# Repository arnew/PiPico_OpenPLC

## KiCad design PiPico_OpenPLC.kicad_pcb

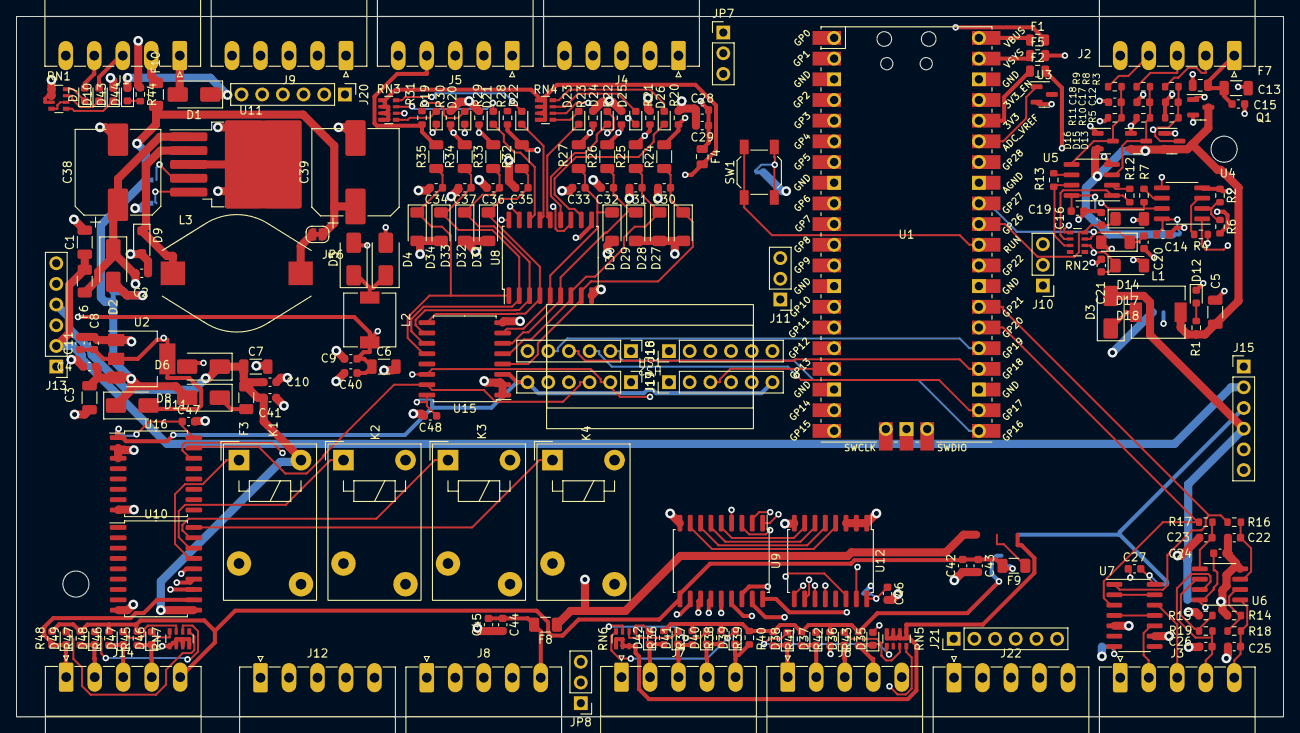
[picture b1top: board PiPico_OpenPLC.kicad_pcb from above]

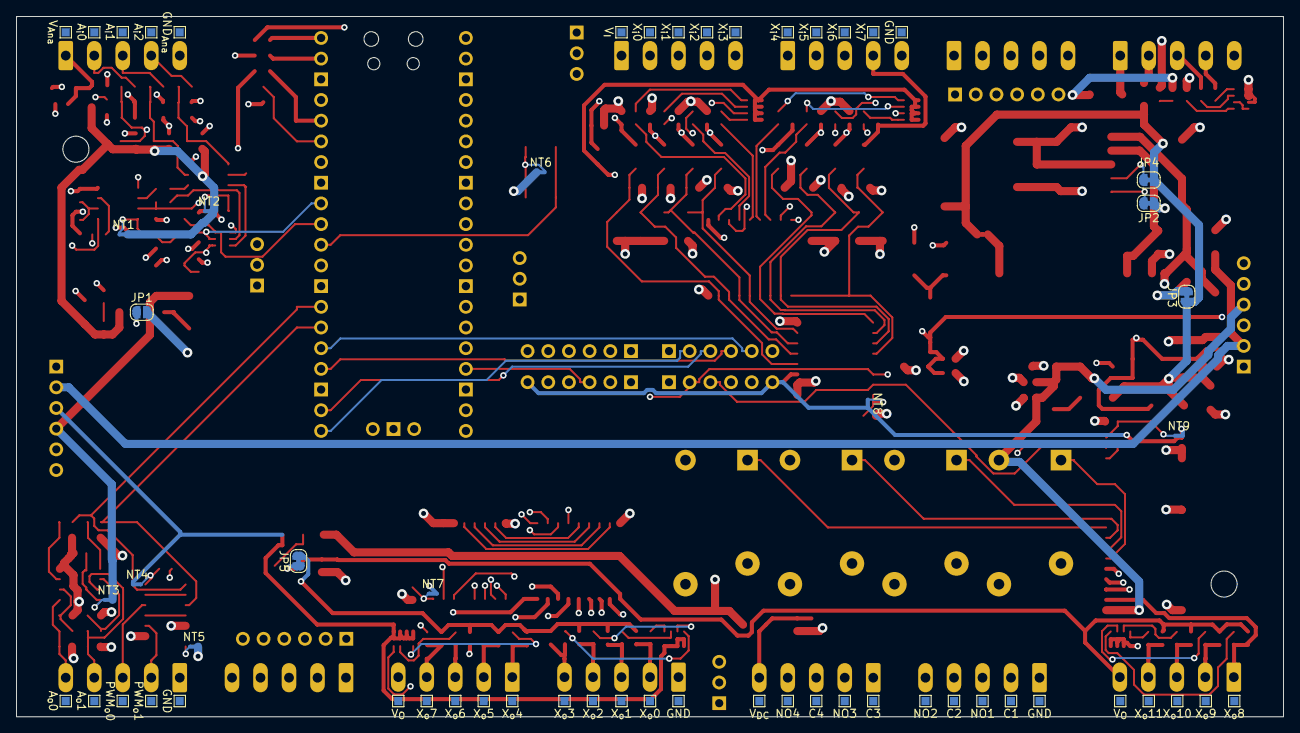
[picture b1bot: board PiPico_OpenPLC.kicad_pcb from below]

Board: 4 copper layers, 155.6 x 86.0 mm, 273 parts (59 on the bottom side), 193 nets.

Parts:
C1, C3, C5, C6, C7, C13: 50V 10uF X5R; C_1206_3216Metric
C2, C4, C9, C10, C11, C14, C15, C19, C24, C27, C29, C43, C44, C46, C47, C48: 50V 100nF X7R; C_0603_1608Metric
C8, C22, C23, C28, C42, C45: 10V 10uF X5R; C_0603_1608Metric
C12, C16, C17, C18, C20, C21, C25, C26, C30, C31, C32, C33, C34, C35, C36, C37, C40, C41: 50V 10nF X7R; C_0603_1608Metric
C38: 220uF 50V 105C; CP_Elec_10x10
C39: 680uF 25V 105C; CP_Elec_10x10.5
D1, D2, D3, D4, D5, D6, D8, D11: SS34; D_SMA
D7, D10, D12, D19, D20, D21, D22, D23, D24, D25, D26, D35, D36, D37, D38, D39, D40, D41, D42, D43, D44, D46, D47, D48, D49: Red; LED_0603_1608Metric
D9: MBR340F; D_SOD-123F
D13, D15, D16: BAV99; SOT-23
D14, D17, D18, D27, D28, D29, D30, D31, D32, D33, D34: ZMM3V3; D_MiniMELF
F1, F2, F4, F5, F7: 33V 100mA; Fuse_0805_2012Metric
F3, F6, F8, F9, F10: 16V 2A; Fuse_1206_3216Metric
H1, H4: MountingHole; MountingHole_3.2mm_M3
HS1, HS2: Submodule
J1, J2, J3, J4, J5, J6, J7, J8, J9, J12, J14, J22: 5 Pin 3.5mm; PhoenixContact_MC_1,5_5-G-3.5_1x05_P3.50mm_Horizontal
J10, J11: Conn_01x03_Male; PinHeader_1x03_P2.54mm_Vertical
J13, J15, J16, J17, J18, J19, J20, J21: Conn_01x06_Male; PinHeader_1x06_P2.54mm_Vertical
JP1: GND <-> GND_{Ana}; SolderJumper-2_P1.3mm_Open_RoundedPad1.0x1.5mm
JP2, JP3, JP4, JP5, JP6: Jumper_2_Bridged; SolderJumper-2_P1.3mm_Bridged_RoundedPad1.0x1.5mm
JP7: 5V < V_{I} > V_{DC}; PinHeader_1x03_P2.54mm_Vertical
JP8: 5V < V_{IO} > V_{DC}; PinHeader_1x03_P2.54mm_Vertical
K1, K2, K3, K4: HF32F/xxx-Z; Relay_SPST_Hongfa_HF32F-Z
L1, L2: 6.8uH; L_6.3x6.3_H3
L3: 150uH 1.5A; L_Bourns_SDR1806
N1: Housing; APRA 449-370-55
NT1, NT2, NT3, NT4, NT5, NT6, NT7, NT8, NT9: NetTie_2; NetTie-2_SMD_Pad0.5mm
Q1: MMBT2222A 1P; SOT-23
R1: 1k; R_0603_1608Metric
R2, R5, R10, R11, R14, R15: 4.3k; R_0603_1608Metric
R3, R4, R6, R7, R8, R9, R12, R13, R16, R17, R18, R19, R20, R21, R22, R23, R28, R29, R30, R31, R44: 10k; R_0603_1608Metric
R24, R25, R26, R27, R32, R33, R34, R35: 4.7k; R_1206_3216Metric
R36, R37, R38, R39, R40, R41, R42, R43, R45, R46, R47, R48: 100k; R_0603_1608Metric
RN1: 1k; R_Array_Convex_4x0603
RN2: 4k7; R_Array_Convex_4x0603
RN3, RN4, RN5, RN6, RN7: 470; R_Array_Convex_4x0603
SW1: TS1187; SW_SPST_SKQG_WithStem
TP1: X_{o}1; TestPoint_Pad_1.0x1.0mm
TP2: X_{o}2; TestPoint_Pad_1.0x1.0mm
TP3: V_{DC}; TestPoint_Pad_1.0x1.0mm
TP4: X_{o}3; TestPoint_Pad_1.0x1.0mm
TP5: X_{o}4; TestPoint_Pad_1.0x1.0mm
TP6: X_{o}5; TestPoint_Pad_1.0x1.0mm
TP7: X_{o}6; TestPoint_Pad_1.0x1.0mm
TP8: X_{o}7; TestPoint_Pad_1.0x1.0mm
TP9: X_{o}8; TestPoint_Pad_1.0x1.0mm
TP10: X_{o}9; TestPoint_Pad_1.0x1.0mm
TP11: X_{o}10; TestPoint_Pad_1.0x1.0mm
TP12: X_{o}11; TestPoint_Pad_1.0x1.0mm
TP13: X_{o}0; TestPoint_Pad_1.0x1.0mm
TP14, TP17, TP27, TP28: GND; TestPoint_Pad_1.0x1.0mm
TP15, TP16: V_{O}; TestPoint_Pad_1.0x1.0mm
TP18: NO4; TestPoint_Pad_1.0x1.0mm
TP19: C4; TestPoint_Pad_1.0x1.0mm
TP20: NO3; TestPoint_Pad_1.0x1.0mm
TP21: C3; TestPoint_Pad_1.0x1.0mm
TP22: NO2; TestPoint_Pad_1.0x1.0mm
TP23: C2; TestPoint_Pad_1.0x1.0mm
TP24: NO1; TestPoint_Pad_1.0x1.0mm
TP25: C1; TestPoint_Pad_1.0x1.0mm
TP26: V_{I}; TestPoint_Pad_1.0x1.0mm
TP29: A_{o}0; TestPoint_Pad_1.0x1.0mm
TP30: A_{o}1; TestPoint_Pad_1.0x1.0mm
TP31: PWM_{o}0; TestPoint_Pad_1.0x1.0mm
TP32: X_{i}7; TestPoint_Pad_1.0x1.0mm
TP33: X_{i}6; TestPoint_Pad_1.0x1.0mm
TP34: X_{i}5; TestPoint_Pad_1.0x1.0mm
TP35: X_{i}4; TestPoint_Pad_1.0x1.0mm
TP36: X_{i}3; TestPoint_Pad_1.0x1.0mm
TP37: X_{i}2; TestPoint_Pad_1.0x1.0mm
TP38: X_{i}1; TestPoint_Pad_1.0x1.0mm
TP39: X_{i}0; TestPoint_Pad_1.0x1.0mm
TP40: PWM_{o}1; TestPoint_Pad_1.0x1.0mm
TP41: V_{Ana}; TestPoint_Pad_1.0x1.0mm
TP42: A_{i}0; TestPoint_Pad_1.0x1.0mm
TP43: A_{i}1; TestPoint_Pad_1.0x1.0mm
TP44: A_{i}2; TestPoint_Pad_1.0x1.0mm
TP45: GND_{Ana}; TestPoint_Pad_1.0x1.0mm
U1: Pico; RPi_Pico_SMD_TH
U2: AMS1117-5.0; SOT-223-3_TabPin2
U3: LM4040DBZ-3; SOT-23
U4, U5, U6: LM358; SOIC-8_3.9x4.9mm_P1.27mm
U7: 74HC14; SOIC-14_3.9x8.7mm_P1.27mm
U8, U9, U10: ULN2803A; SOIC-18W_7.5x11.6mm_P1.27mm
U11: LM2596S-12; TO-263-5_TabPin3
U12, U15, U16: PCF8574; SOIC-16W_7.5x10.3mm_P1.27mm

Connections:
+3V3: D7.2 (A), F2.2, J1.4, J10.1, J13.5, J15.5, J16.6, J17.6, J18.6, J19.6, NT7.2, NT8.2, NT9.2, U15.3 (A2), U16.1 (A0)
+5V: C8.1, C11.1, D4.2 (A), D10.2 (A), D11.2 (A), J1.3, U2.2 (VO)
+10V: C13.1, C15.1, F7.2, J2.1, TP41.1
+12V: C3.1, C4.1, C39.1, D8.2 (A), D11.1 (K), D43.2 (A), F10.2, JP3.1 (A), JP4.1 (A), JP6.1 (A), U2.3 (VI)
/1-Wire: J10.2, U1.29 (GPIO22)
/ADC0: C16.1, D14.1 (K), RN2.8 (R1.2), U1.31 (GPIO26_ADC0)
/ADC1: C20.1, D17.1 (K), RN2.7 (R2.2), U1.32 (GPIO27_ADC1)
/ADC2: C21.1, D18.1 (K), RN2.6 (R3.2), U1.34 (GPIO28_ADC2)
/Analog_Input/Ai0: J2.2, R3.1, TP42.1
/Analog_Input/Ai1: J2.3, R8.1, TP43.1
/Analog_Input/Ai2: J2.4, R9.1, TP44.1
/Analog_Output/Ao0: C25.1, J3.5, R18.2, TP29.1, U6.1
/Analog_Output/Ao1: C26.1, J3.4, R19.2, TP30.1, U6.7
/Di0: C30.1, D27.1 (K), R24.1, U8.8 (I8), U15.4 (P0)
/Di1: C31.1, D28.1 (K), R25.1, U8.7 (I7), U15.5 (P1)
/Di2: C32.1, D29.1 (K), R26.1, U8.6 (I6), U15.6 (P2)
/Di3: C33.1, D30.1 (K), R27.1, U8.5 (I5), U15.7 (P3)
/Di4: C35.1, D31.1 (K), R32.1, U8.4 (I4), U15.9 (P4)
/Di5: C36.1, D32.1 (K), R33.1, U8.3 (I3), U15.10 (P5)
/Di6: C37.1, D33.1 (K), R34.1, U8.2 (I2), U15.11 (P6)
/Di7: C34.1, D34.1 (K), R35.1, U8.1 (I1), U15.12 (P7)
/Digital_Input/Xi0: J4.2, R20.1, R24.2, TP39.1
/Digital_Input/Xi1: J4.3, R21.1, R25.2, TP38.1
/Digital_Input/Xi2: J4.4, R22.1, R26.2, TP37.1
/Digital_Input/Xi3: J4.5, R23.1, R27.2, TP36.1
/Digital_Input/Xi4: J5.1, R28.1, R32.2, TP35.1
/Digital_Input/Xi5: J5.2, R29.1, R33.2, TP34.1
/Digital_Input/Xi6: J5.3, R30.1, R34.2, TP33.1
/Digital_Input/Xi7: J5.4, R31.1, R35.2, TP32.1
/Digital_Output/Xo0: D42.1 (K), J7.2, R36.1, TP13.1, U9.11 (O8)
/Digital_Output/Xo1: D41.1 (K), J7.3, R37.1, TP1.1, U9.12 (O7)
/Digital_Output/Xo2: D40.1 (K), J7.4, R38.1, TP2.1, U9.13 (O6)
/Digital_Output/Xo3: D39.1 (K), J7.5, R39.1, TP4.1, U9.14 (O5)
/Digital_Output/Xo4: D38.1 (K), J6.1, R40.1, TP5.1, U9.15 (O4)
/Digital_Output/Xo5: D37.1 (K), J6.2, R41.1, TP6.1, U9.16 (O3)
/Digital_Output/Xo6: D36.1 (K), J6.3, R42.1, TP7.1, U9.17 (O2)
/Digital_Output/Xo7: D35.1 (K), J6.4, R43.1, TP8.1, U9.18 (O1)
/Digital_Output/Xo8: D49.1 (K), J14.1, R48.1, TP9.1, U10.11 (O8)
/Digital_Output/Xo9: D48.1 (K), J14.2, R47.1, TP10.1, U10.12 (O7)
/Digital_Output/Xo10: D47.1 (K), J14.3, R46.1, TP11.1, U10.13 (O6)
/Digital_Output/Xo11: D46.1 (K), J14.4, R45.1, TP12.1, U10.14 (O5)
/Digital_Output/Zo_0: J12.3, K1.NO, TP24.1
/Digital_Output/Zo_1: J12.5, K2.NO, TP22.1
/Digital_Output/Zo_2: J8.2, K3.NO, TP20.1
/Digital_Output/Zo_3: J8.4, K4.NO, TP18.1
/Digital_Output/Zp_0: J12.2, K1.C, TP25.1
/Digital_Output/Zp_1: J12.4, K2.C, TP23.1
/Digital_Output/Zp_2: J8.1, K3.C, TP21.1
/Digital_Output/Zp_3: J8.3, K4.C, TP19.1
/Digital_Output/z0: K1.A1, U10.15 (O4)
/Digital_Output/z1: K2.A1, U10.16 (O3)
/Digital_Output/z2: K3.A1, U10.17 (O2)
/Digital_Output/z3: K4.A1, U10.18 (O1)
/Do0: U9.8 (I8), U12.4 (P0)
/Do1: U9.7 (I7), U12.5 (P1)
/Do2: U9.6 (I6), U12.6 (P2)
/Do3: U9.5 (I5), U12.7 (P3)
/Do4: U9.4 (I4), U12.9 (P4)
/Do5: U9.3 (I3), U12.10 (P5)
/Do6: U9.2 (I2), U12.11 (P6)
/Do7: U9.1 (I1), U12.12 (P7)
/Do8: U10.8 (I8), U16.4 (P0)
/Do9: U10.7 (I7), U16.5 (P1)
/Do10: U10.6 (I6), U16.6 (P2)
/Do11: U10.5 (I5), U16.7 (P3)
/Do12: U10.4 (I4), U16.9 (P4)
/Do13: U10.3 (I3), U16.10 (P5)
/Do14: U10.2 (I2), U16.11 (P6)
/Do15: U10.1 (I1), U16.12 (P7)
/I2C0_SCL: J17.2, U1.7 (GPIO5), U12.14 (SCL), U15.14 (SCL), U16.14 (SCL)
/I2C0_SDA: J17.3, U1.6 (GPIO4), U12.15 (SDA), U15.15 (SDA), U16.15 (SDA)
/I2C1_SCL: J18.2, U1.5 (GPIO3)
/I2C1_SDA: J18.3, U1.4 (GPIO2)
/PWMo0: R17.1, U1.26 (GPIO20), U7.3
/PWMo1: R16.1, U1.27 (GPIO21), U7.1
/Powersupply/+12V_prefilter: D9.1 (K), L3.1, U11.2 (OUT)
/SPI0_CSn: J16.3, U1.22 (GPIO17)
/SPI0_RX: J16.2, U1.21 (GPIO16)
/SPI0_SCK: J16.4, U1.24 (GPIO18)
/SPI0_TX: J16.5, U1.25 (GPIO19)
/SPI1_CSn: J19.3, U1.17 (GPIO13)
/SPI1_RX: J19.2, U1.16 (GPIO12)
/SPI1_SCK: J19.4, U1.19 (GPIO14)
/SPI1_TX: J19.5, U1.20 (GPIO15)
/UART0_RX: J17.4, U1.2 (GPIO1)
/UART0_TX: J17.5, U1.1 (GPIO0)
/UART1_RX: J18.4, U1.12 (GPIO9)
/UART1_TX: J18.5, U1.11 (GPIO8)
ADC_VREF: R4.1, U1.35 (ADC_VREF), U3.1 (K)
GND: C1.2, C2.2, C3.2, C4.2, C6.2, C7.2, C8.2, C9.2, C10.2, C11.2, C22.2, C23.2, C24.2, C25.2, C26.2, C28.1, C29.2, C30.2, C31.2, C32.2, C33.2, C34.2, C35.2, C36.2, C37.2, C38.2, C39.2, C40.2, C41.2, C42.1, C43.2, C44.2, C45.1, C46.2, C47.2, C48.2, D9.2 (A), D27.2 (A), D28.2 (A), D29.2 (A), D30.2 (A), D31.2 (A), D32.2 (A), D33.2 (A), D34.2 (A), J1.5, J3.1, J5.5, J7.1, J10.3, J12.1, J13.6, J15.6, J16.1, J17.1, J18.1, J19.1, J20.6, J21.6, JP1.2 (B), JP2.1 (A), NT5.2, NT6.1, R14.1, R15.1, R20.2, R21.2, R22.2, R23.2, R28.2, R29.2, R30.2, R31.2, R44.1, RN1.1 (R1.1), RN1.2 (R2.1), RN1.3 (R3.1), TP14.1, TP17.1, TP27.1, TP28.1, U1.3 (GND), U1.8 (GND), U1.13 (GND), U1.18 (GND), U1.23 (GND), U1.28 (GND), U1.38 (GND), U2.1 (GND), U6.4 (V-), U7.5, U7.9, U8.9 (GND), U9.9 (GND), U10.9 (GND), U11.3 (GND), U12.1 (A0), U12.2 (A1), U12.3 (A2), U12.8 (VSS), U15.1 (A0), U15.2 (A1), U15.8 (VSS), U16.2 (A1), U16.3 (A2), U16.8 (VSS)
GNDA: C5.2, C12.2, C13.2, C14.2, C15.2, C16.2, C17.2, C18.2, C19.2, C20.2, C21.2, D12.1 (K), D13.1 (K), D14.2 (A), D15.1 (K), D16.1 (K), D17.2 (A), D18.2 (A), J2.5, JP1.1 (A), R2.1, R5.1, R10.1, R11.1, TP45.1, U1.33 (AGND), U3.2 (A), U4.4 (V-), U5.4 (V-)
unnamed: D1.2 (A), J1.1
unnamed: D2.2 (A), JP3.2 (B)
unnamed: D3.1 (K), L1.1
unnamed: D4.1 (K), D5.1 (K), L2.1
unnamed: D7.1 (K), RN1.8 (R1.2)
unnamed: D8.1 (K), F3.1
unnamed: D10.1 (K), RN1.7 (R2.2)
unnamed: D12.2 (A), R1.1
unnamed: D19.2 (A), RN3.5 (R4.2)
unnamed: D19.1 (K), U8.18 (O1)
unnamed: D20.2 (A), RN3.6 (R3.2)
unnamed: D20.1 (K), U8.17 (O2)
unnamed: D21.2 (A), RN3.7 (R2.2)
unnamed: D21.1 (K), U8.16 (O3)
unnamed: D22.2 (A), RN3.8 (R1.2)
unnamed: D22.1 (K), U8.15 (O4)
unnamed: D23.2 (A), RN4.5 (R4.2)
unnamed: D23.1 (K), U8.14 (O5)
unnamed: D24.2 (A), RN4.6 (R3.2)
unnamed: D24.1 (K), U8.13 (O6)
unnamed: D25.2 (A), RN4.7 (R2.2)
unnamed: D25.1 (K), U8.12 (O7)
unnamed: D26.2 (A), RN4.8 (R1.2)
unnamed: D26.1 (K), U8.11 (O8)
unnamed: D35.2 (A), RN5.8 (R1.2)
unnamed: D36.2 (A), RN5.7 (R2.2)
unnamed: D37.2 (A), RN5.6 (R3.2)
unnamed: D38.2 (A), RN5.5 (R4.2)
unnamed: D39.2 (A), RN6.8 (R1.2)
unnamed: D40.2 (A), RN6.7 (R2.2)
unnamed: D41.2 (A), RN6.6 (R3.2)
unnamed: D42.2 (A), RN6.5 (R4.2)
unnamed: D43.1 (K), RN1.5 (R4.2)
unnamed: D44.1 (K), R44.2
unnamed: D46.2 (A), RN7.8 (R1.2)
unnamed: D47.2 (A), RN7.7 (R2.2)
unnamed: D48.2 (A), RN7.6 (R3.2)
unnamed: D49.2 (A), RN7.5 (R4.2)
unnamed: F10.1, J1.2
unnamed: J3.2, TP40.1, U7.10
unnamed: J3.3, TP31.1, U7.12
unnamed: C28.2, C29.1, F4.1, J4.1, TP26.1
unnamed: C44.1, C45.2, F8.2, J8.5, TP3.1
unnamed: J11.1, U1.41 (SWCLK)
unnamed: J11.2, U1.42 (GND)
unnamed: J11.3, U1.43 (SWDIO)
unnamed: C42.2, C43.1, F9.2, J6.5, J14.5, JP5.1 (A), TP15.1, TP16.1, U9.10 (COM)
unnamed: J9.1, J20.1
unnamed: J9.2, J20.2
unnamed: J9.3, J20.3
unnamed: J9.4, J20.4
unnamed: J9.5, J20.5
unnamed: J21.1, J22.1
unnamed: J21.2, J22.2
unnamed: J21.3, J22.3
unnamed: J21.4, J22.4
unnamed: J21.5, J22.5
unnamed: JP2.2 (B), U11.5 (~ON/OFF)
unnamed: JP4.2 (B), U11.4 (FB)
unnamed: JP5.2 (B), R36.2, R37.2, R38.2, R39.2, R40.2, R41.2, R42.2, R43.2, R45.2, R46.2, R47.2, R48.2
unnamed: JP6.2 (B), L3.2
unnamed: F4.2, JP7.2 (C)
unnamed: F9.1, JP8.2 (C)
unnamed: NT6.2, SW1.2
unnamed: Q1.1 (B), U4.1
unnamed: F7.1, Q1.2 (E), R6.2
unnamed: RN1.4 (R4.1), RN1.6 (R3.2)
unnamed: R7.2, RN2.1 (R1.1), U4.7
unnamed: R12.2, RN2.2 (R2.1), U5.1
unnamed: R13.2, RN2.3 (R3.1), U5.7
unnamed: F2.1, U1.36 (3V3)
unnamed: SW1.1, U1.30 (RUN)
unnamed: F1.1, U1.40 (VBUS)
unnamed: F5.1, U1.39 (VSYS)
unnamed: R4.2, U4.3 (+)
unnamed: R2.2, R6.1, U4.2 (-)
unnamed: C12.1, D13.3 (K), R3.2, R5.2, U4.5 (+)
unnamed: R7.1, U4.6 (-)
unnamed: C14.1, NT1.1, U4.8 (V+)
unnamed: C17.1, D15.3 (K), R8.2, R10.2, U5.3 (+)
unnamed: R12.1, U5.2 (-)
unnamed: C18.1, D16.3 (K), R9.2, R11.2, U5.5 (+)
unnamed: R13.1, U5.6 (-)
unnamed: C19.1, NT2.1, U5.8 (V+)
unnamed: C22.1, R16.2, U6.3 (+)
unnamed: R14.2, R18.1, U6.2 (-)
unnamed: C23.1, R17.2, U6.5 (+)
unnamed: R15.2, R19.1, U6.6 (-)
unnamed: C24.1, NT3.1, U6.8 (V+)
unnamed: U7.4, U7.11
unnamed: U7.2, U7.13
unnamed: C27.1, NT5.1, U7.7 (GND)
unnamed: C27.2, NT4.2, U7.14 (VCC)
unnamed: C46.1, NT7.1, U12.16 (VDD)
unnamed: C48.1, NT8.1, U15.16 (VDD)
unnamed: C47.1, NT9.1, U16.16 (VDD)
VAA: C5.1, D13.2 (A), D15.2 (A), D16.2 (A), L1.2, NT1.2, NT2.2, Q1.3 (C), R1.2
VBUS: D5.2 (A), D6.2 (A), F1.2
VCC: C6.1, C9.1, C40.1, F5.2, J13.3, J15.3, JP7.3 (B), JP8.3 (B), L2.2, NT4.1, RN3.1 (R1.1), RN3.2 (R2.1), RN3.3 (R3.1), RN3.4 (R4.1), RN4.1 (R1.1), RN4.2 (R2.1), RN4.3 (R3.1), RN4.4 (R4.1), RN5.1 (R1.1), RN5.2 (R2.1), RN5.3 (R3.1), RN5.4 (R4.1), RN6.1 (R1.1), RN6.2 (R2.1), RN6.3 (R3.1), RN6.4 (R4.1), RN7.1 (R1.1), RN7.2 (R2.1), RN7.3 (R3.1), RN7.4 (R4.1), U8.10 (COM)
VCCQ: C7.1, C10.1, C41.1, D3.2 (A), D6.1 (K), F3.2, J13.4, J15.4, K1.A2, K2.A2, K3.A2, K4.A2, NT3.2, U10.10 (COM)
VDC: C1.1, D1.1 (K), D44.2 (A), F6.1, J13.2, J15.2
VPP: C2.1, C38.1, D2.1 (K), F6.2, F8.1, JP7.1 (A), JP8.1 (A), U11.1 (VIN)

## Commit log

2023-04-06 initial project data import
2023-04-06 routed version
2023-05-01 snap
2023-06-12 Preparation for future use.
    Reworked to use i2c bus expanders.
    added sketch for add-on boards.
2024-01-30 Added Submodule, changed Ports to i2c
